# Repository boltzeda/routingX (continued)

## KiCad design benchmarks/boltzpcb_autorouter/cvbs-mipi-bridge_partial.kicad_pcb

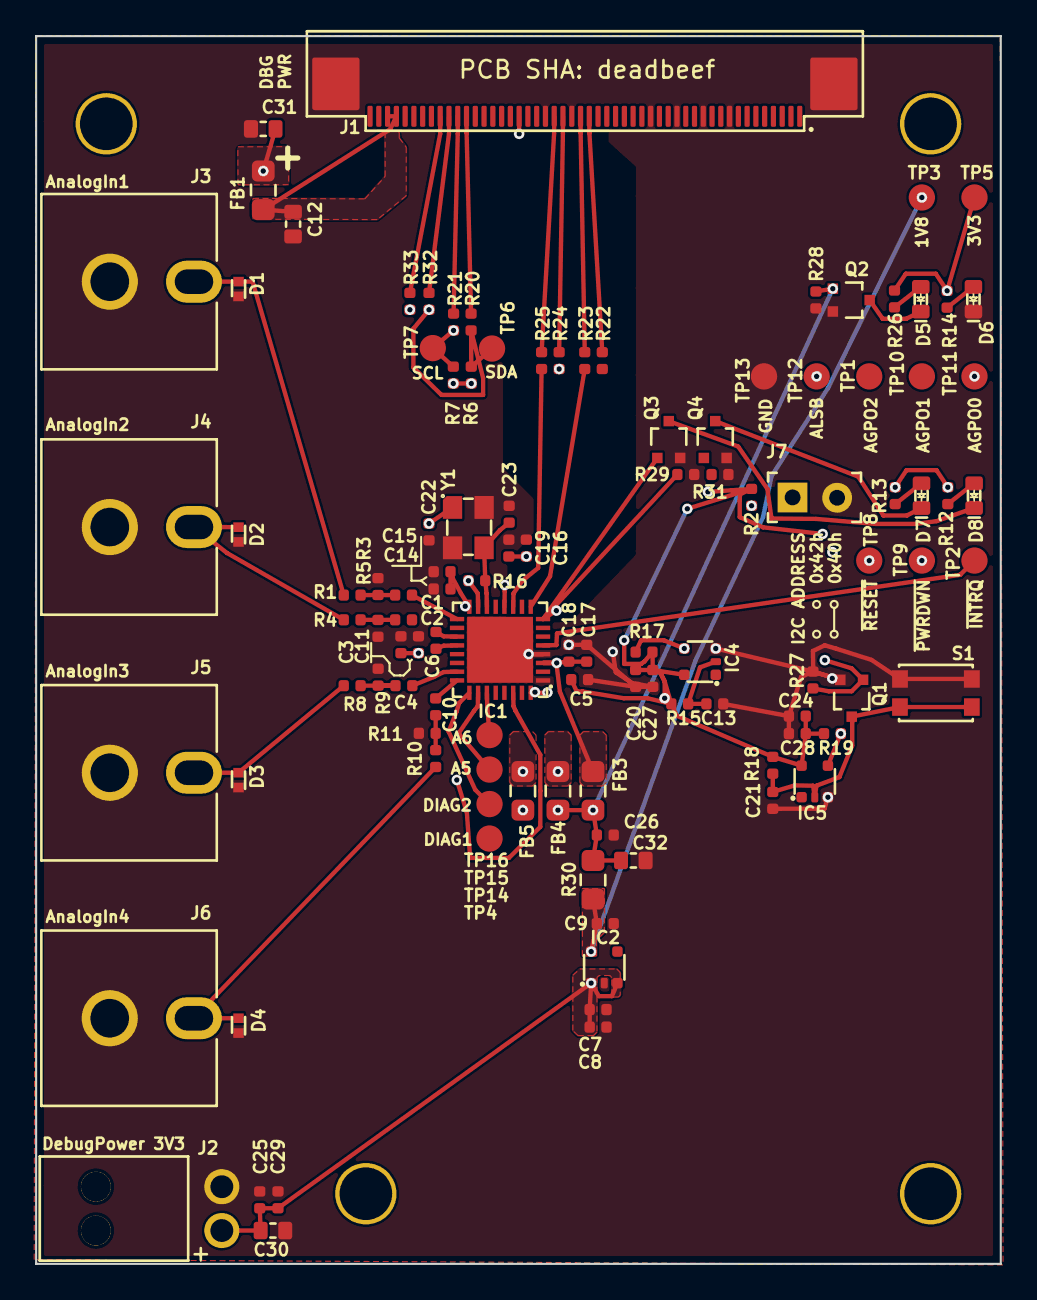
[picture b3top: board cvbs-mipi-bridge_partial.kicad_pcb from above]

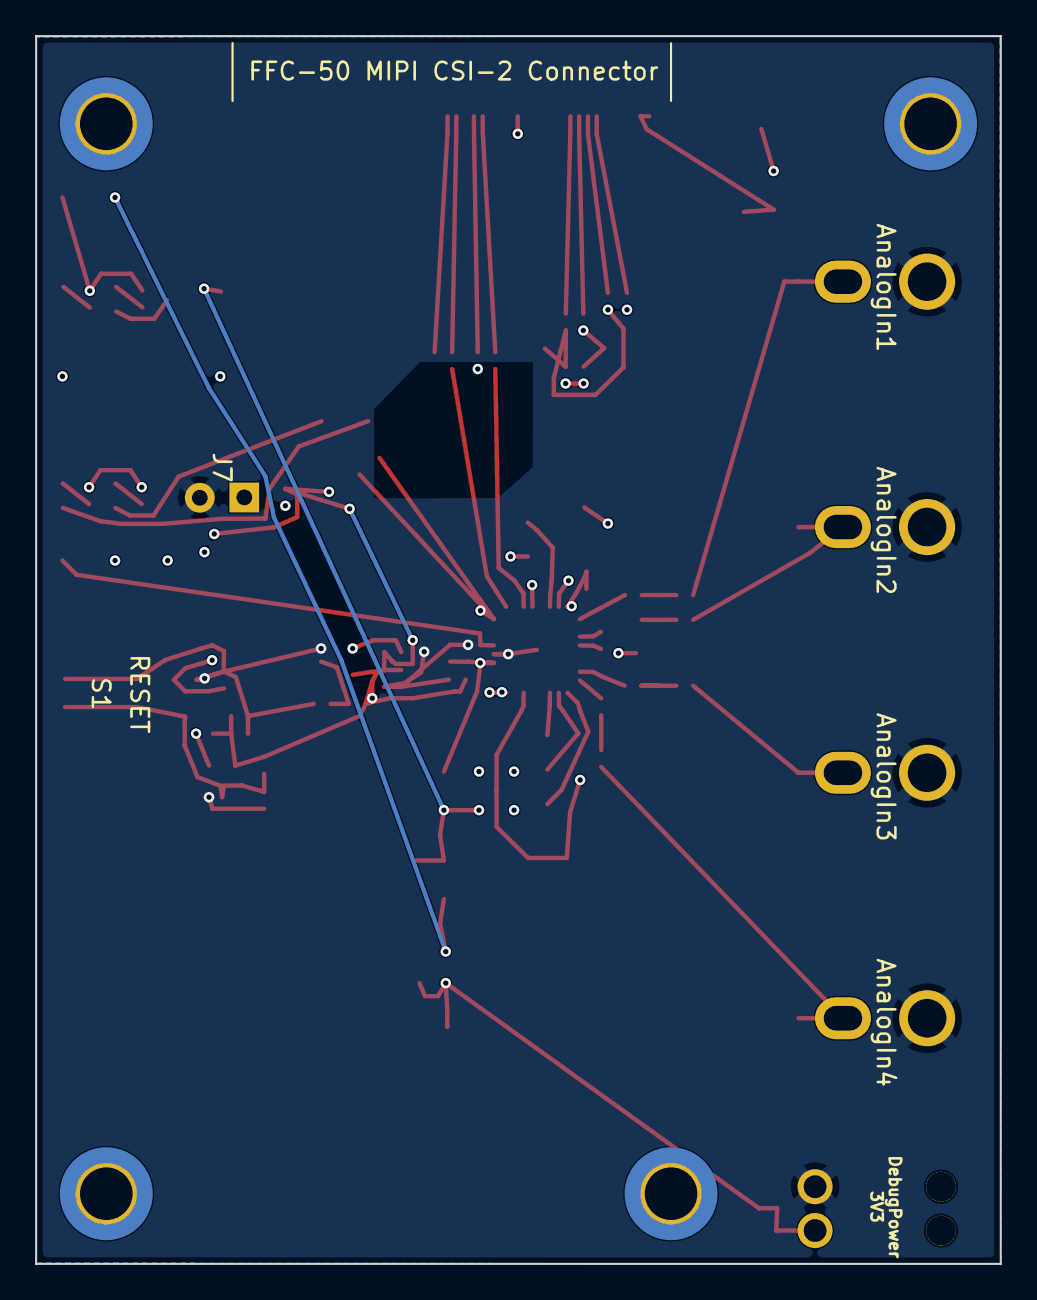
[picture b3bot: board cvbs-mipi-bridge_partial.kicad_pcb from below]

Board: 4 copper layers, 55.0 x 70.0 mm, 114 parts (4 on the bottom side), 59 nets.

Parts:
C1, C2, C3, C4, C5, C6, C7, C10, C13, C14, C16, C17, C20, C21, C24, C26, C29: C_100n_0402; C_0402_1005Metric
C8, C9, C25, C27, C28: C_1u_0402; C_0402_1005Metric
C11, C15, C18, C19: C_10n_0402; C_0402_1005Metric
C12: C_1u_0603; C_0603_1608Metric
C22, C23: C_10p_0402; C_0402_1005Metric
C30, C31, C32: C_10u_0603; C_0603_1608Metric
D1, D2, D3, D4: UCLAMP2501T.TCT; SLP1006P2T
D5, D6, D7, D8: LED_G_0603_KP-1608ZGC; LED_0603_1608Metric_G
FB1, FB3, FB4, FB5: FB_220Z_1.5A_WE-CBF_0805; FB_0805_2012Metric
IC1: ADV7282-M; LFCSP-32-1EP-5x5mm
IC2: TLV70018_SC70; SC-70-5
IC4, IC5: SN74AUP1G17_SC70; SC-70-5
J1: Conn_FFC_WE_68715014522; Conn_FFC_WE_68715014x22
J2: Molex_Nano-Fit_1x2_1053131102; Conn_Molex_Nano-Fit_1x2_1053131102
J3, J4, J5, J6: RCA_Jack_KLPX-0848A-2-Y
J7: PinHeader_1x2_P2.54mm_Drill1.1mm; PinHeader_1x2_P2.54_Drill0.9mm
MP1, MP2, MP3, MP4: Spacer_Drill3mm_H3mm_9774030243R
Q1, Q2, Q3, Q4: BSS138PW; SC70-3
R1, R4, R8, R10: R_24R_0402; R_0402_1005Metric
R2: R_1k_0402; R_0402_1005Metric
R3, R5, R9, R11: R_51R_0402; R_0402_1005Metric
R6, R7: R_4k7_0402; R_0402_1005Metric
R12, R13, R14, R26: R_470R_0402; R_0402_1005Metric
R15: R_22k_0402; R_0402_1005Metric
R16: R_1M_0402; R_0402_1005Metric
R17, R18, R19, R27, R28, R29, R31: R_100k_0402; R_0402_1005Metric
R20, R21, R22, R23, R24, R25, R32, R33: R_0R_0402; R_0402_1005Metric
R30: R_0R_0805; R_0805_2012Metric
S1: SW_KMR211NGLFS_SMD
TP1, TP2, TP3, TP4, TP5, TP6, TP7, TP8, TP9, TP10, TP11, TP12, TP13, TP14, TP15, TP16: TP_1.5mm_SMD; TP_SMD_1.5mm
Y1: Resonator_28.63636MHz_ABM8G; Oscillator_SMD_Geyer_KX-7-4Pin_3.2x2.5mm

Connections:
1V8_SYS: C26.1, C32.1, FB3.1, FB4.1, FB5.1, Q2.1 (G), R28.2, R30.2
3V3_SYS: C5.1, C7.1, C8.1, C20.1, C24.2, C25.1, C27.2, C28.1, C29.1, C30.1, C31.1, FB1.1, IC1.2 (DVDDIO), IC2.1 (VIN), IC2.3 (EN), IC4.5 (VCC), IC5.5 (VCC), J2.1, R2.1, R6.2, R7.2, R12.2, R13.2, R14.1, R15.2, R17.2, R18.2, R19.2, R26.1, TP5.1
/AGPO0: IC1.8 (GPO0), Q3.1 (G), R29.2, TP11.1
/AGPO1: IC1.7 (GPO1), Q4.1 (G), R31.2, TP10.1
/AGPO2: IC1.6 (GPO2), TP1.1
/AIN1: C1.2, IC1.17 (AIN1)
/AIN1_C: C1.1, R1.2, R3.2
/AIN1_ESD: D1.2 (A), J3.1, R1.1
/AIN2: C2.2, IC1.18 (AIN2)
/AIN2_C: C2.1, R4.2, R5.2
/AIN2_ESD: D2.2 (A), J4.1, R4.1
/AIN3: C4.2, IC1.23 (AIN3)
/AIN3_C: C4.1, R8.2, R9.2
/AIN3_ESD: D3.2 (A), J5.1, R8.1
/AIN4: C10.2, IC1.24 (AIN4)
/AIN4_C: C10.1, R10.2, R11.2
/AIN4_ESD: D4.2 (A), J6.1, R10.1
/ALSB: IC1.29 (ALSB), J7.1, R2.2, TP12.1
/CSI_A_CLK_N: IC1.12 (CLK_N), R24.1
/CSI_A_CLK_P: IC1.11 (CLK_P), R25.1
/CSI_A_CLK_R_N: J1.28, R24.2
/CSI_A_CLK_R_P: J1.29, R25.2
/CSI_A_D0_N: IC1.10 (D0_N), R22.1
/CSI_A_D0_P: IC1.9 (D0_P), R23.1
/CSI_A_D0_R_N: J1.25, R22.2
/CSI_A_D0_R_P: J1.26, R23.2
/PWRDWN: IC1.32 (~PWRDWN), IC4.4 (Y), R17.1, TP9.1
/RESET: IC1.28 (~RESET), IC5.4 (Y), R19.1, TP8.1
/RST_IN: J1.33, Q1.1 (G), R27.2
/SCL: IC1.31 (SCLK), R7.1, R21.1, R33.1, TP7.1
/SDA: IC1.30 (SDATA), R6.1, R20.1, R32.1, TP6.1
/VREFN: C6.2, IC1.20 (VREFN)
/VREFP: C6.1, IC1.19 (VREFP)
/XTAL_N: C22.1, IC1.15 (XTALN), R16.1, Y1.1
/XTAL_P: C23.1, IC1.14 (XTALP), R16.2, Y1.3
/~INTRQ: IC1.5 (~INTRQ), TP2.1
AVDD_1V8: C14.1, C15.2, FB4.2, IC1.16 (PVDD)
DVDD_1V8: C16.1, C17.1, C18.2, C19.1, FB3.2, IC1.3 (DVDD), IC1.13 (MVDD)
GND: C3.2, C5.2, C7.2, C8.2, C9.2, C11.1, C12.2, C13.1, C14.2, C15.1, C16.2, C17.2, C18.1, C19.2, C20.2, C21.2, C22.2, C23.2, C24.1, C25.2, C26.2, C27.1, C28.2, C29.2, C30.2, C31.2, C32.2, D1.1 (K), D2.1 (K), D3.1 (K), D4.1 (K), D6.2, IC1.1 (DGND), IC1.4 (DGND), IC1.33 (EP), IC2.2 (GND), IC4.3 (GND), IC5.3 (GND), J1.9, J1.12, J1.15, J1.18, J1.27, J1.30, J1.MP1 (MP), J1.MP2 (MP), J2.2, J3.2, J4.2, J5.2, J6.2, J7.2, Q1.2 (S), Q2.2 (S), Q3.2 (S), Q4.2 (S), R3.1, R5.1, R9.1, R11.1, R27.1, R28.1, R29.1, R31.1, S1.1, S1.2, TP13.1, Y1.2 (SH), Y1.4 (SH)
unnamed: C12.1, FB1.2, J1.47, J1.48
unnamed: D5.1, R26.2
unnamed: D6.1, R14.2
unnamed: D7.1, R13.1
unnamed: D8.1, R12.1
unnamed: IC1.26 (AIN5), TP15.1
unnamed: IC1.27 (AIN6), TP16.1
unnamed: IC1.22 (DIAG1), TP4.1
unnamed: IC1.25 (DIAG2), TP14.1
unnamed: C9.1, IC2.5 (VOUT), R30.1, TP3.1
unnamed: C13.2, IC4.2 (A), R15.1
unnamed: C21.1, IC5.2 (A), Q1.3 (D), R18.1, S1.3, S1.4
unnamed: J1.39, R20.2
unnamed: J1.40, R21.2
unnamed: J1.41, R32.2
unnamed: J1.42, R33.2
unnamed: D5.2, Q2.3 (D)
unnamed: D8.2, Q3.3 (D)
unnamed: D7.2, Q4.3 (D)
PVDD_1V8: C3.1, C11.2, FB5.2, IC1.21 (AVDD)

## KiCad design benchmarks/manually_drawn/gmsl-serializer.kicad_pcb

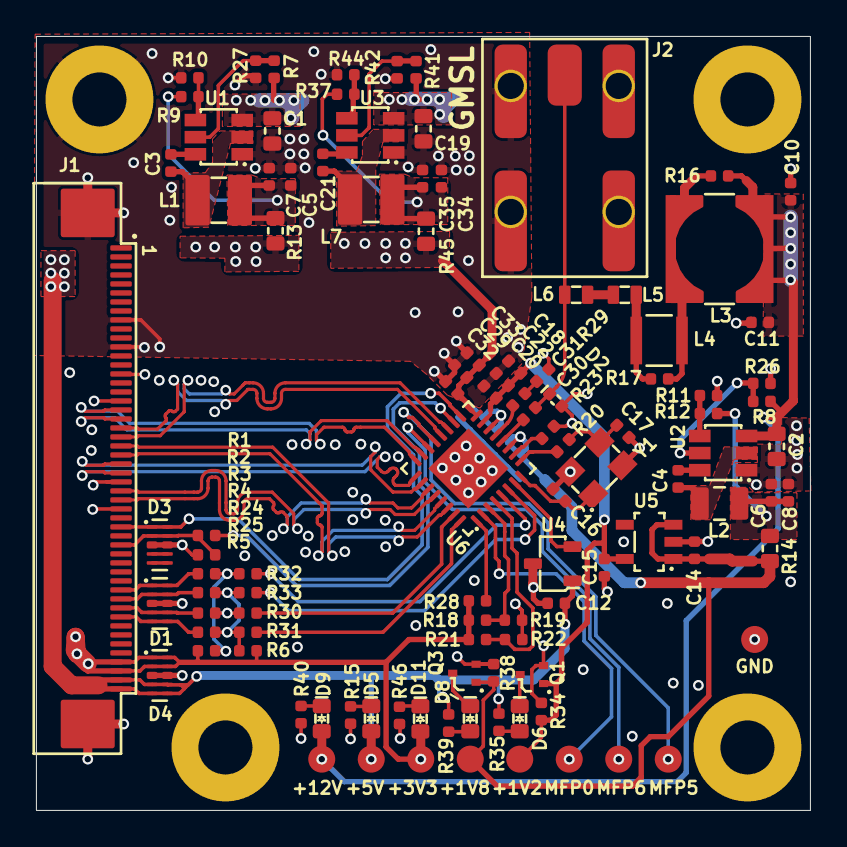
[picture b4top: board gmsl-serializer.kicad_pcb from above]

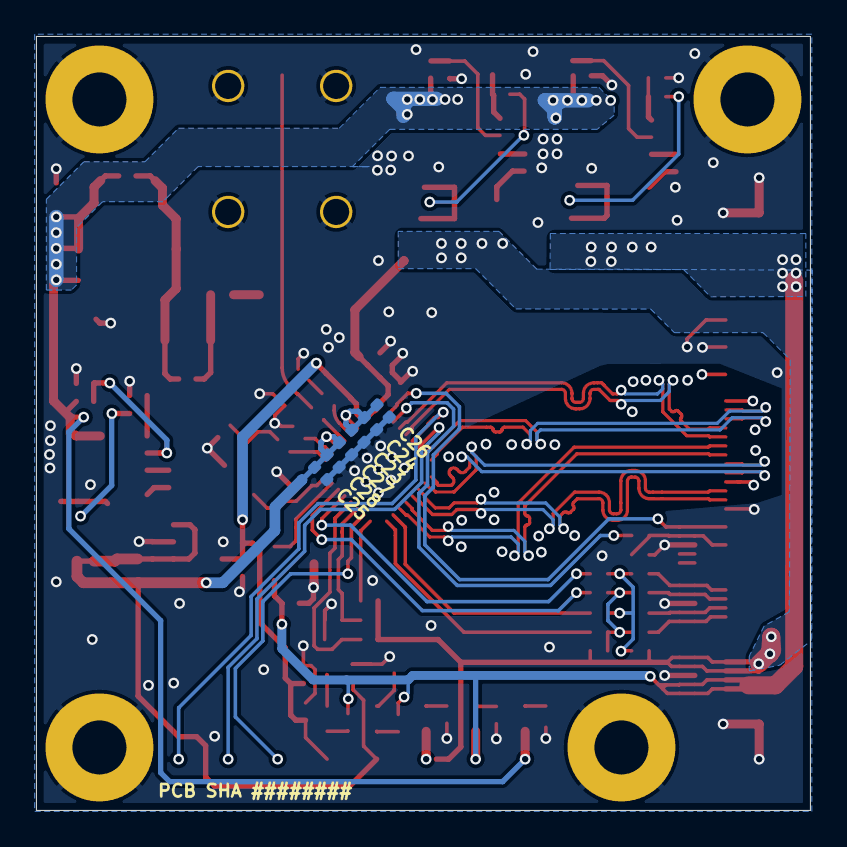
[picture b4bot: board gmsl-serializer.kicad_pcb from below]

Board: 4 copper layers, 43.0 x 43.0 mm, 118 parts (6 on the bottom side), 70 nets.

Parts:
C1, C2, C19: C_10u_25V_0603; C_0603_1608Metric
C3, C21: C_220n_0402; C_0402_1005Metric
C4, C10, C20, C22, C24, C30, C31: C_100n_0402; C_0402_1005Metric
C5, C6, C7, C8, C34, C35: C_22u_0402; C_0402_1005Metric
C11, C23, C27, C28, C29, C32: C_10n_0402; C_0402_1005Metric
C12, C14, C15: C_1u_16V_0402; C_0402_1005Metric
C16, C17: C_33p_0402; C_0402_1005Metric
C18, C25, C26, C33: C_10u_0402; C_0402_1005Metric
D1, D3, D4: PESD4USB5U-TTS; DFN-10_2.5x1mm
D2: AXGD10402KR; D_0402_1005Metric
D5, D6, D8, D9, D11: LED_G_0603_LTST-C190GKT; LED_0603_1608Metric_G
J1: Conn_FFC_WE_68715014022; Conn_FFC_WE_68715014x22
J2: Conn_FAKRA_59S2AQ-40MT5-Z_1
L1, L7: L_3u3_3.1A_Bourns-SRP3212A; L_Bourns-SRP3212A
L2: L_1u_2.6A_0806; L_0806_2016Metric
L3: L_22u_1.12A_Coilcraft-MSS6132T; L_Coilcraft-MSS6132T
L4: L_6u8_1A_Coilcraft-1210POC; L_Coilcraft-1210POC
L5, L6: L_470n_1A_Coilcraft-PFL1609; L_Coilcraft-PFL1609
MP1, MP2, MP3, MP4: MP_Pad6mm_Drill3mm
N1: antmicro_logo; antmicro-logo_scaled_12mm_mask
Q1, Q3: DMG1012T-7; SOT-523
R1, R7, R8, R10, R12, R19, R21, R22, R26, R27, R28, R41, R42, R44: R_10k_0402; R_0402_1005Metric
R2: R_12k_0402; R_0402_1005Metric
R3, R4, R24, R25: R_100R_0402; R_0402_1005Metric
R5, R6: R_4k7_0402; R_0402_1005Metric
R9: R_52k3_0402; R_0402_1005Metric
R11: R_12k4_0402; R_0402_1005Metric
R13, R14, R45: R_0R_22.4A_0603; R_0603_1608Metric
R15, R35, R39: R_470R_0402; R_0402_1005Metric
R16, R17: R_5k1_0402; R_0402_1005Metric
R18: R_80k6_0402; R_0402_1005Metric
R20, R30, R31, R32, R33: R_0R_0402; R_0402_1005Metric
R23: R_402R_0402; R_0402_1005Metric
R29: R_51R_0402; R_0402_1005Metric
R34, R38: R_100k_0402; R_0402_1005Metric
R37: R_31k6_0402; R_0402_1005Metric
R40: R_1k65_0402; R_0402_1005Metric
R46: R_200R_0402; R_0402_1005Metric
TP1, TP2, TP3, TP4, TP5, TP6, TP7, TP8, TP9: TP_1.5mm_SMD; TP_SMD_1.5mm
U1, U2, U3: AP62301_TSOT; TSOT23-6
U4: REF3012AIDBZT; SOT-23-3
U5: TLV73312PDBVT; SOT-23-5
U6: MAX96717GTJ_VY+; TQFN-32-1EP_5x5mm_P0.5mm
Y1: Resonator_25MHz_ABM8G; Resonator_SMD_Abracon_ABM8G_3.2x2.5mm

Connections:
+1V2: C15.2, C18.2, C20.2, C22.2, Q1.1 (G), R34.2, TP5.1, U5.5 (VOUT), U6.15 (VDD)
+1V8: C14.2, C25.2, C27.2, C28.2, Q3.1 (G), R14.2, R38.2, TP2.1, U5.1 (VIN), U5.3 (EN), U6.11 (VDD18)
+3V3: C29.2, C32.2, C33.2, D4.1, D4.2, D4.9, D4.10, D11.2 (A), J1.47, J1.48, R5.2, R6.2, R18.2, R21.2, R28.2, R45.2, TP4.1, U6.16 (VDDIO)
+5V: C12.2, D4.4, D4.5, D4.6, D4.7, D5.2 (A), J1.49, J1.50, R13.2, R35.2, R39.2, TP1.1, U4.1 (IN)
+12V: C1.2, C2.2, C10.2, C11.2, C19.2, D9.2 (A), L3.1, R7.2, R8.2, R16.1, R41.2, TP3.1, U1.3 (VIN), U2.3 (VIN), U3.3 (VIN)
/CSI Connector/CSI.CLK_N: J1.28, U6.28 (CKN)
/CSI Connector/CSI.CLK_P: J1.29, U6.27 (CKP)
/CSI Connector/CSI.D0_N: J1.25, U6.26 (D0N)
/CSI Connector/CSI.D0_P: J1.26, U6.25 (D0P)
/CSI Connector/CSI.D1_N: J1.23, U6.30 (D1N)
/CSI Connector/CSI.D1_P: J1.24, U6.29 (D1P)
/CSI Connector/CSI.D2_N: J1.21, U6.20 (D2N)
/CSI Connector/CSI.D2_P: J1.22, U6.19 (D2P)
/CSI Connector/CSI.D3_N: J1.19, U6.24 (D3N)
/CSI Connector/CSI.D3_P: J1.20, U6.23 (D3P)
/CSI Connector/GPIO3: D3.1, D3.10, J1.32, U6.17 (MFP3)
/CSI Connector/GPIO4: R1.2, U6.18 (MFP4)
/CSI Connector/GPIO4_1V8: D3.2, D3.9, J1.34, R1.1, R2.1
/CSI Connector/I2C.SCL: R4.2, R6.1, R25.2, R31.1, R33.1
/CSI Connector/I2C.SDA: R3.2, R5.1, R24.2, R30.1, R32.1
/CSI Connector/SCL_CAM0: D1.2, D1.9, J1.40, R4.1
/CSI Connector/SCL_CAM1: D1.5, D1.6, J1.42, R25.1
/CSI Connector/SDA_CAM0: D1.1, D1.10, J1.39, R3.1
/CSI Connector/SDA_CAM1: D1.4, D1.7, J1.41, R24.1
/GMSL Connector/SIO_P: C30.2, D2.1 (C), J2.1, L6.2
/Serializer/CFG0: R18.1, R19.2, U6.3 (MFP1)
/Serializer/CFG1: R21.1, R22.2, U6.4 (MFP2)
/Serializer/VREF: U4.2 (OUT), U6.7 (VREF)
/Serializer/X1: C16.2, U6.8 (X1/OSC), Y1.1
/Serializer/X2: R20.2, U6.9 (X2)
/Serializer/X2_R: C17.2, R20.1, Y1.3
/Supply/EN_1V8: R8.1, R26.2, U2.5 (EN)
/Supply/EN_3V3: R41.1, R42.2, U3.5 (EN)
/Supply/EN_5V: R7.1, R27.2, U1.5 (EN)
/Supply/FB_1V8: R11.1, R12.2, U2.4 (FB)
/Supply/FB_3V3: R37.1, R44.2, U3.4 (FB)
/Supply/FB_5V: R9.1, R10.2, U1.4 (FB)
/Supply/OUT_1V8: C6.2, C8.2, L2.2, R11.2, R14.1
/Supply/OUT_3V3: C34.2, C35.2, L7.2, R37.2, R45.1
/Supply/OUT_5V: C5.2, C7.2, L1.2, R9.2, R13.1
/Supply/SW_1V8: C4.2, L2.1, U2.2 (SW)
/Supply/SW_3V3: C21.2, L7.1, U3.2 (SW)
/Supply/SW_5V: C3.2, L1.1, U1.2 (SW)
GND: C1.1, C2.1, C5.1, C6.1, C7.1, C8.1, C10.1, C11.1, C12.1, C14.1, C15.1, C16.1, C17.1, C18.1, C19.1, C20.1, C22.1, C23.1, C24.1, C25.1, C26.1, C27.1, C28.1, C29.1, C32.1, C33.1, C34.1, C35.1, D1.3, D1.8, D2.2 (A), D3.3, D3.8, D4.3, D4.8, J1.9, J1.12, J1.15, J1.18, J1.27, J1.30, J1.MP1 (MP), J1.MP2 (MP), J2.2, J2.3, J2.4, J2.5, MP1.1, MP2.1, MP3.1, MP4.1, Q1.2 (S), Q3.2 (S), R2.2, R10.1, R12.1, R15.1, R19.1, R22.1, R23.1, R26.1, R27.1, R29.1, R34.1, R38.1, R40.1, R42.1, R44.1, R46.1, TP9.1, U1.1 (GND), U2.1 (GND), U3.1 (GND), U4.3 (GND), U5.2 (GND), U6.33 (GND), Y1.2 (SH), Y1.4 (SH)
unnamed: C31.2, R29.2
unnamed: D5.1 (C), R15.2
unnamed: D6.2 (A), R35.1
unnamed: D6.1 (C), Q1.3 (D)
unnamed: D8.2 (A), R39.1
unnamed: D8.1 (C), Q3.3 (D)
unnamed: D9.1 (C), R40.2
unnamed: D11.1 (C), R46.2
unnamed: L3.2, L4.1, R16.2, R17.1
unnamed: L4.2, L5.1, R17.2
unnamed: L5.2, L6.1
unnamed: C3.1, U1.6 (BST)
unnamed: C4.1, U2.6 (BST)
unnamed: C21.1, U3.6 (BST)
unnamed: C23.2, C24.2, C26.2, U6.14 (CAP_VDD)
unnamed: TP6.1, U6.2 (MFP0)
unnamed: TP7.1, U6.21 (MFP5)
unnamed: TP8.1, U6.22 (MFP6)
unnamed: R30.2, U6.31 (MFP7)
unnamed: R31.2, U6.32 (MFP8)
unnamed: R32.2, U6.5 (MFP9)
unnamed: R33.2, U6.6 (MFP10)
unnamed: R28.1, U6.1 (PWDNB)
unnamed: C31.1, U6.13 (SION)
unnamed: C30.1, U6.12 (SIOP)
unnamed: R23.2, U6.10 (XRES)

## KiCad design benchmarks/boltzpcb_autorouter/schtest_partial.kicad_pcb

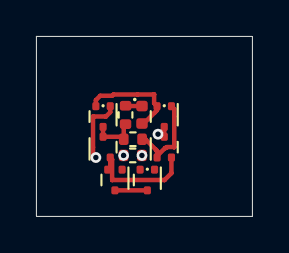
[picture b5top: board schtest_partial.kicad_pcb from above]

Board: 4 copper layers, 12.0 x 10.0 mm, 10 parts (0 on the bottom side), 8 nets.

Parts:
D1: LED; LED_0402_1005Metric_COMPACT
N1, N2, N3: 2SK3541; SOT-723-COMPACT
P1, P2, P3: RZM001P02T2L; SOT-723-COMPACTP
R1, R2, R3: 1k; R_0402_1005Metric_COMPACT

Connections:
B0NQ: N1.3 (D), P1.3 (D), R1.1, R3.2
B0Q: N2.3 (D), N3.1 (G), P2.3 (D), P3.1 (G), R2.1
B0R: N2.1 (G), P2.1 (G), R1.2
B0S: N1.1 (G), P1.1 (G), R2.2
GND: N1.2 (S), N2.2 (S), N3.2 (S)
unnamed: D1.1 (K), R3.1
unnamed: N3.3 (D), P3.3 (D)
VDD: D1.2 (A), P1.2 (S), P2.2 (S), P3.2 (S)

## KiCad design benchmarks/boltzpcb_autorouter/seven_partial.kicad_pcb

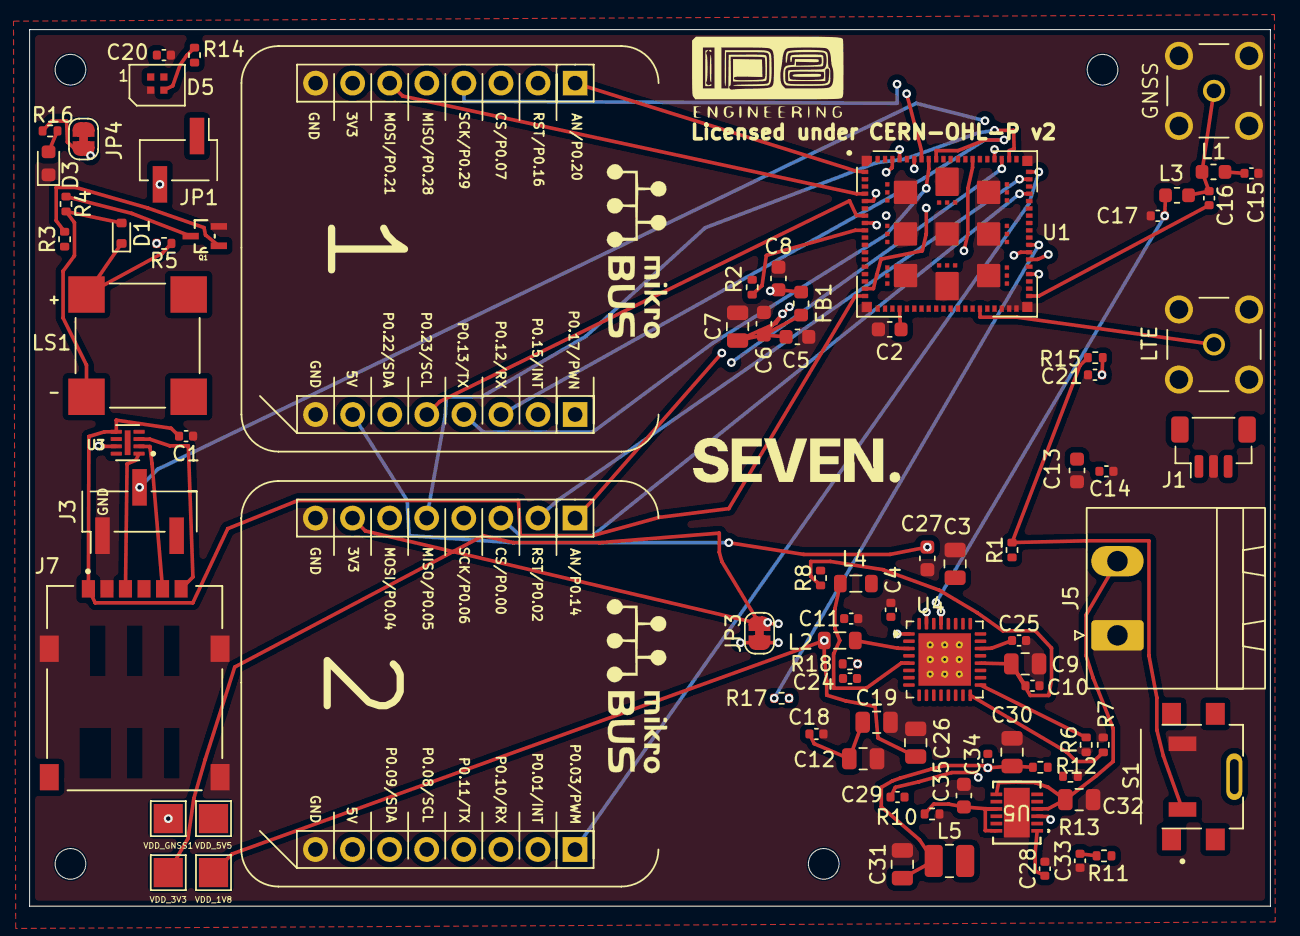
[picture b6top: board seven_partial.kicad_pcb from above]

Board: 4 copper layers, 85.0 x 60.0 mm, 83 parts (0 on the bottom side), 76 nets.

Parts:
C1: 10nF; C_0402_1005Metric
C2, C13: 4.7uF; C_0603_1608Metric
C3, C5, C6, C8, C35: 1.0uF; C_0603_1608Metric
C4, C14, C20, C21, C29: 100nF; C_0402_1005Metric
C7, C9, C12, C19, C26, C27, C32: 10uF; C_0805_2012Metric
C10, C18, C24, C25: 1.0nF; C_0402_1005Metric
C11, C15: N.C.; C_0402_1005Metric
C16, C17: 39pF; C_0402_1005Metric
C28: 22nF; C_0402_1005Metric
C30: 47uF; C_0805_2012Metric
C31: 22uF; C_0805_2012Metric
C33: 470pF; C_0402_1005Metric
C34: 27pF; C_0402_1005Metric
D1: BAT54KFILM; D_SOD-523
D3: LED; LED_0603_1608Metric
D5: SK6805-EC15; LED_SK6805_EC15-PLCC4
FB1: 22Ω @ 100MHz; L_0603_1608Metric
J1: JST_SH_BM03B-SRSS-TB_1x03; JST_SH_BM03B-SRSS-TB_1x03-1MP_P1.00mm_Vertical
J3: Conn_01x03; PinHeader_1x03_P2.54mm_Vertical_SMD_Pin1Left
J5: Conn_01x02; PhoenixContact_MSTBA_2,5_2-G-5,08_1x02_P5.08mm_Horizontal
J7: NSIM-2-C; CUI_NSIM-2-C
J8: GNSS; LPRS_SMA_CONNECTOR
J9: LTE; LPRS_SMA_CONNECTOR
JP1: Current measurement; PinHeader_1x02_P2.54mm_Vertical_SMD_Pin1Left
JP3, JP4: SolderJumper_2_Bridged; SolderJumper-2_P1.3mm_Bridged_RoundedPad1.0x1.5mm
L1: N.C.; L_0603_1608Metric
L2, L4: 2.2uH; L_0805_2012Metric
L3: 68nH; L_0603_1608Metric
L5: 22uH; L_1008_2520Metric
LS1: CMT-8504-100-SMT-TR; XDCR_CMT-8504-100-SMT-TR
Q1: MMST3904-7-F; SOT65P210X110-3N
R1, R2: 10k; R_0402_1005Metric
R3: 300; R_0402_1005Metric
R4, R5, R8: 0; R_0402_1005Metric
R6: 47k; R_0402_1005Metric
R7: 250k; R_0402_1005Metric
R10: DNP; R_0402_1005Metric
R11: 100k; R_0402_1005Metric
R12: 90.9k; R_0402_1005Metric
R13: 12.4k; R_0402_1005Metric
R14: 220; R_0402_1005Metric
R15, R16: 1k; R_0402_1005Metric
R17, R18: 4k7; R_0402_1005Metric
S1: TL3336AF160Q; SW_TL3336AF160Q
U1: nRF9151-LAXX; LGA_9151_12.1x11.1mm
U3: TPD3F303DPVR; SON50P210X160X65-9N
U4: nPM1300-QEXX; QFN-32-1EP_5x5mm_P0.5mm_EP3.6x3.6mm_ThermalVias
U5: ISL85410FRZ-T7A; DFN12_L12.4X3_REN
VDD_1V8: VDD_1V8; TestPoint_Pad_2.0x2.0mm
VDD_3V3: VDD_3V3; TestPoint_Pad_2.0x2.0mm
VDD_5V5: VDD_5V_OUT; TestPoint_Pad_2.0x2.0mm
VDD_GNSS1: VDD_GNSS; TestPoint_Pad_2.0x2.0mm
mB1, mB3: mikroBUS_socket_left
mB2, mB4: mikroBUS_socket_right

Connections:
/Antenna GNSS/GNSS_ANTENNA: C16.2, U1.42 (GPS)
/Antenna LTE/LTE_ANTENNA: J9.1, U1.35 (ANT)
/Buzzer/BUZZER: R3.1, U1.80 (P0.19/AIN6)
/JST-SH Contact/SWCLK: J1.1 (SWCLK), U1.3 (SWDCLK)
/JST-SH Contact/SWDIO: J1.3 (SWDIO), U1.4 (SWDIO)
/MCU/AN1: U1.2 (P0.20/AIN7), mB3.9 (AN)
/MCU/AN2: U1.74 (P0.14/AIN1), mB1.9 (AN)
/MCU/CS1: U1.64 (P0.07), mB3.11 (CS)
/MCU/CS2: U1.56 (P0.00), mB1.11 (CS)
/MCU/I2C_SCL1: U1.8 (P0.23/TRACEDATA1), mB4.4 (SCL)
/MCU/I2C_SCL2: U1.67 (P0.08), mB2.4 (SCL)
/MCU/I2C_SDA1: U1.6 (P0.22/TRACEDATA0), mB4.3 (SDA)
/MCU/I2C_SDA2: U1.68 (P0.09), mB2.3 (SDA)
/MCU/INT1: U1.75 (P0.15/AIN2), mB4.7 (INT)
/MCU/INT2: U1.57 (P0.01), mB2.7 (INT)
/MCU/PWM1: U1.78 (P0.17/AIN4), mB4.8 (PWM)
/MCU/PWM2: U1.59 (P0.03), mB2.8 (PWM)
/MCU/RST1: U1.77 (P0.16/AIN3), mB3.10 (RST)
/MCU/RST2: U1.58 (P0.02), mB1.10 (RST)
/MCU/SCL: R18.1, U1.50 (P0.31), U4.14 (SCL)
/MCU/SDA: R17.1, U1.49 (P0.30), U4.13 (SDA)
/MCU/SIM_1V8: C1.1, J7.C1 (VCC), U1.19 (SIM_1V8), U3.5 (VCC)
/MCU/SIM_CLK: U1.18 (SIM_CLK), U3.7 (CLK_IN)
/MCU/SIM_IO: U1.17 (SIM_IO), U3.6 (DATA2_IN)
/MCU/SIM_RST: U1.16 (SIM_RST), U3.8 (DATA1_IN)
/MCU/SPI_MISO1: U1.47 (P0.28), mB3.13 (MISO)
/MCU/SPI_MISO2: U1.62 (P0.05), mB1.13 (MISO)
/MCU/SPI_MOSI1: U1.5 (P0.21/TRACECLK), mB3.14 (MOSI)
/MCU/SPI_MOSI2: U1.61 (P0.04), mB1.14 (MOSI)
/MCU/SPI_SCK1: U1.48 (P0.29), mB3.12 (SCK)
/MCU/SPI_SCK2: U1.63 (P0.06), mB1.12 (SCK)
/MCU/SYSTEM_LED: R14.1, U1.79 (P0.18/AIN5)
/MCU/UART_RX: J3.3 (TX), U1.44 (P0.26)
/MCU/UART_RX1: U1.73 (P0.13/AIN0), mB4.5 (TX)
/MCU/UART_RX2: U1.70 (P0.11), mB2.5 (TX)
/MCU/UART_TX: J3.2 (RX), U1.45 (P0.27)
/MCU/UART_TX1: U1.72 (P0.12), mB4.6 (RX)
/MCU/UART_TX2: U1.69 (P0.10), mB2.6 (RX)
/MCU/nRESET: R1.2, R15.2, S1.1
GND: C1.2, C2.1, C3.2, C4.2, C5.2, C6.2, C7.2, C8.2, C9.2, C10.2, C11.2, C12.2, C13.2, C14.2, C15.1, C17.1, C18.2, C19.2, C20.2, C21.2, C24.2, C25.2, C26.2, C27.2, C28.2, C30.2, C31.2, C32.2, C33.1, C35.1, D3.1 (K), D5.2 (VSS), J1.2 (GND), J3.1 (GND), J5.1 (GND), J7.C5 (GND), J7.SH1 (GND), J7.SH2 (GND), J7.SH3 (GND), J8.G1, J8.G2, J8.G3, J8.G4, J9.G1, J9.G2, J9.G3, J9.G4, Q1.2, R6.1, R7.1, R10.2, R13.1, S1.2, U1.1 (GND), U1.7 (GND), U1.13 (GND), U1.15 (GND), U1.20 (GND), U1.25 (GND), U1.30 (GND), U1.34 (GND), U1.36 (GND), U1.38 (GND), U1.39 (GND), U1.40 (GND), U1.41 (GND), U1.43 (GND), U1.46 (GND), U1.51 (GND), U1.55 (GND), U1.60 (GND), U1.66 (GND), U1.71 (GND), U1.76 (GND), U1.105 (GND), U1.106 (GND), U1.107 (GND), U1.108 (GND), U1.109 (GND), U1.110 (GND), U1.111 (GND), U1.112 (GND), U1.113 (GND), U3.9 (GND), U4.2 (PVSS1), U4.6 (PVSS2), U4.33 (AVSS), U5.6 (PGND), U5.13 (GND), mB1.16 (GND), mB2.1 (GND), mB3.16 (GND), mB4.1 (GND)
unnamed: C15.2, L1.1
unnamed: C16.1, J8.1, L1.2, L3.2
unnamed: C33.2, R11.2
unnamed: D1.1 (A), LS1.P, R5.1
unnamed: D1.2 (K), LS1.N, R4.2
unnamed: D3.2 (A), R16.2
unnamed: D5.3 (DIN), R14.2
unnamed: C32.1, J5.2 (VIN), U5.4 (VIN), U5.7 (EN)
unnamed: J7.C3 (CLK), U3.2 (CLK_OUT)
unnamed: J7.C7 (I/O), U3.3 (DATA2_OUT)
unnamed: J7.C2 (RST), U3.1 (DATA1_OUT)
unnamed: JP1.1 (A), R2.2, U1.14 (VDD)
unnamed: C8.1, FB1.2, JP1.2 (B)
unnamed: Q1.1, R3.2
unnamed: Q1.3, R4.1
unnamed: C2.2, U1.24 (DEC0)
unnamed: R2.1, U1.10 (ENABLE)
unnamed: C21.1, R15.1, U1.9 (~RESET)
unnamed: C11.1, C12.1, C18.1, C19.1, C24.1, R8.2, U4.4 (PVDD)
unnamed: L2.2, U4.3 (SW1)
unnamed: L4.2, U4.5 (SW2)
unnamed: C25.1, U4.22 (VBUSOUT)
unnamed: R6.2, U4.17 (VSET1)
unnamed: R7.2, U4.16 (VSET2)
unnamed: C9.1, C10.1, R8.1, U4.20 (VSYS)
unnamed: C29.1, U5.3 (BOOT)
unnamed: R11.1, U5.11 (COMP)
unnamed: C34.2, R12.1, R13.2, U5.10 (FB)
unnamed: C35.2, R10.1, U5.9 (VCC), U5.12 (FS)
unnamed: C29.2, L5.2, U5.5 (PHASE)
unnamed: C28.1, U5.1 (SS)
VDD_1V8: C26.1, L2.1, U4.1 (VOUT1), VDD_1V8.1 (1_1)
VDD_3V3: C4.1, C13.1, C14.1, C27.1, JP3.2 (B), JP4.2 (B), L4.1, R1.1, R17.2, R18.2, U1.65 (VDD_GPIO), U4.12 (VDDIO), U4.28 (LSIN1/VINLDO1), U4.30 (LSIN2/VINLDO2), U4.32 (VOUT2), VDD_3V3.1 (1_1), mB1.15 (+3.3V), mB3.15 (+3.3V)
VDD_5V: C3.1, C5.1, C6.1, C7.1, C20.1, C30.1, C31.1, C34.1, D5.4 (VDD), FB1.1, L5.1, R5.2, R12.2, U4.21 (VBUS), VDD_5V5.1, mB2.2 (+5V), mB4.2 (+5V)
VDD_GNSS: C17.2, JP3.1 (A), L3.1, U4.29 (LSOUT1/VOUTLDO1), VDD_GNSS1.1 (1_1)
VDD_POWER_LED: JP4.1 (A), R16.1, U4.31 (LSOUT2/VOUTLDO2)
